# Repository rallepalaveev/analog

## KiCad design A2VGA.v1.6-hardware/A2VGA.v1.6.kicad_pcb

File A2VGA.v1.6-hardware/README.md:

A2VGA

This project is a new hardware implementation of the work done by Mark Aikens and David Kuder of the VGA analog card for Apple2.

The card is based on RPI Pico, 74LVC245 chips and a PLD. It is all through-hole. An improvement is that an ATF22V10 is used, which has sufficient I/O lines to allow that all necessaty bits of the address bus (A0-A10) are decoded for correct switching off of the ExtROM, in case the RPI firmware is using this memory. Additionally, the nLRESET signal can be fed to pin 30 of the Pico via a jumper, in case it is needed by future firmwares.

This v1.6 has IRQ capability and supports the A2USB firmware written by ThorstenB - https://github.com/ThorstenBr/A2USB 

Acknowledgements

This is a fork of David Kuder V2RetroComputing and ∀2 Retro Computing project with a new board design intended to fully support his software. The original design was posted by Mark Aikens Apple II VGA.

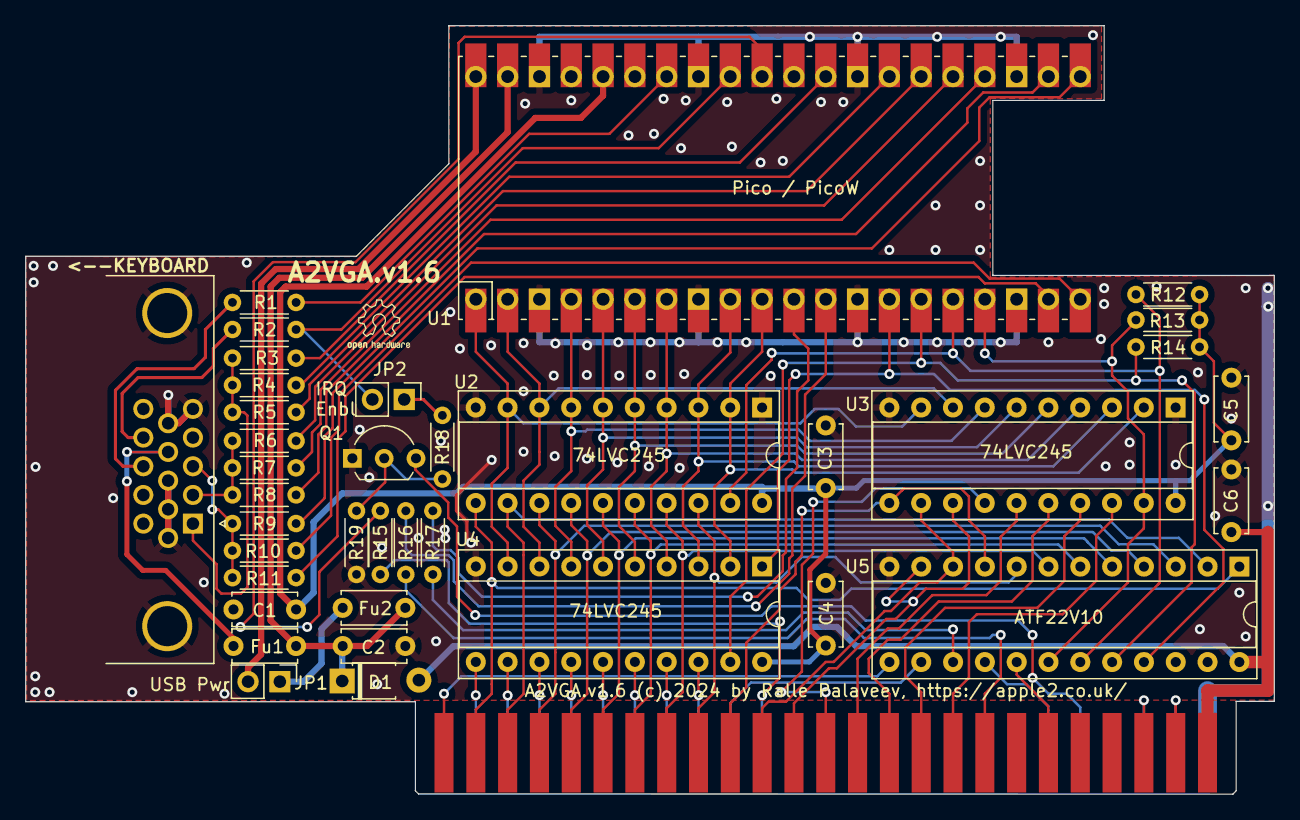
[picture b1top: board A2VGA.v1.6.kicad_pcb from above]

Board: 2 copper layers, 99.7 x 61.4 mm, 37 parts (0 on the bottom side), 49 nets.

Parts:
C1, C2, C3, C4, C5, C6: 100n; C_Disc_D5.0mm_W2.5mm_P5.00mm
CON2: DB15_Female_HighDensity_MountingHoles; DSUB-15-HD_Female_Horizontal_P2.29x1.98mm_EdgePinOffset3.03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
D1: D_T-1_P5.08mm_Horizontal
Fu1, Fu2: 500mA; C_Disc_D5.0mm_W2.5mm_P5.00mm
JP1, JP2: PinHeader_1x02_P2.54mm_Vertical
Q1: 2N7000; TO-92L_Inline_Wide
R1, R2: 47; R_Axial_DIN0204_L3.6mm_D1.6mm_P5.08mm_Horizontal
R3, R6, R9: 510; R_Axial_DIN0204_L3.6mm_D1.6mm_P5.08mm_Horizontal
R4, R7, R10, R15, R16, R17, R18: 1k; R_Axial_DIN0204_L3.6mm_D1.6mm_P5.08mm_Horizontal
R5, R8, R11: 2k; R_Axial_DIN0204_L3.6mm_D1.6mm_P5.08mm_Horizontal
R12, R13, R14, R19: 10k; R_Axial_DIN0204_L3.6mm_D1.6mm_P5.08mm_Horizontal
U1: Pico / PicoW; RPi_PicoW_SMD_TH
U2, U3, U4: 74LVC245; DIP-20_W7.62mm_Socket
U5: ATF22V10; DIP-24_W7.62mm_Socket

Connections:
3.3V: C1.1, C3.1, C4.1, C5.1, R12.2, R13.2, R14.2, U1.36 (3V3), U2.20, U3.20, U4.20
5V: C6.2, D1.2, U5.24
A0: U2.11, U5.1
A1: U2.12, U5.2
A2: U2.13, U5.3
A3: U2.14, U5.4
A4: U2.15, U5.5
A5: U2.16, U5.6
A6: U2.17, U5.7
A7: U2.18, U5.8
A8: U3.11, U5.9
A9: U3.12, U5.10
A10: U3.13, U5.11
B0: R9.2, U1.21 (GPIO16)
B1: R10.2, U1.20 (GPIO15)
B2: R11.2, U1.19 (GPIO14)
B_out: CON2.3, R9.1, R10.1, R11.1
DATADIR: U1.14 (GPIO10), U4.1, U5.21
DATAOE: R14.1, U1.15 (GPIO11), U4.19, U5.20
Enable: R17.1, U5.15
G0: R6.2, U1.25 (GPIO19)
G1: R7.2, U1.24 (GPIO18)
G2: R8.2, U1.22 (GPIO17)
GND: C1.2, C2.1, C3.2, C4.2, C5.2, C6.1, CON2.0, CON2.5, CON2.6, CON2.7, CON2.8, CON2.10, Q1.1, R19.1, U1.3 (GND), U1.8 (GND), U1.13 (GND), U1.18 (GND), U1.23 (GND), U1.28 (GND), U1.33 (AGND), U1.38 (GND), U2.1, U2.10, U3.1, U3.10, U4.10, U5.12
G_out: CON2.2, R6.1, R7.1, R8.1
HSYNC: R1.2, U1.34 (GPIO28_ADC2)
HS_out: CON2.13, R1.1
L-ENBL: R17.2, U1.11 (GPIO8)
L-PHI0: R15.2, U1.31 (GPIO26_ADC0)
L-RW: R16.2, U1.12 (GPIO9)
LD0: U1.1 (GPIO0), U2.9, U3.9, U4.9
LD1: U1.2 (GPIO1), U2.8, U3.8, U4.8
LD2: U1.4 (GPIO2), U2.7, U3.7, U4.7
LD3: U1.5 (GPIO3), U2.6, U3.6, U4.6
LD4: U1.6 (GPIO4), U2.5, U3.5, U4.5
LD5: U1.7 (GPIO5), U2.4, U3.4, U4.4
LD6: U1.9 (GPIO6), U2.3, U3.3, U4.3
LD7: U1.10 (GPIO7), U2.2, U3.2, U4.2
LSBOE: R12.1, U1.16 (GPIO12), U2.19, U5.19
MSBOE: R13.1, U1.17 (GPIO13), U3.19, U5.18
R0: R3.2, U1.29 (GPIO22)
R1: R4.2, U1.27 (GPIO21)
R2: R5.2, U1.26 (GPIO20)
RGB-PWR: CON2.9, Fu1.1
R_out: CON2.1, R3.1, R4.1, R5.1
VBUS: JP1.2, U1.40 (VBUS)
VSYNC: JP2.2, R2.2, U1.32 (GPIO27_ADC1)
VSYS: C2.2, D1.1, Fu1.2, Fu2.2, U1.39 (VSYS)
VS_out: CON2.14, R2.1

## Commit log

2024-07-07 Rename A2VGA.v1.6-hardware/v2-analog-preloader.uf2 to A2VGA.v1.6-hardware/firmwares/v2-analog-preloader.uf2
2024-07-07 Rename A2VGA.v1.6-hardware/A2USB-MOUSE-PAL-A2VGA-4ns-v1.3.uf2 to A2VGA.v1.6-hardware/firmwares/A2USB-MOUSE-PAL-A2VGA-4ns-v1.3.uf2
2024-07-07 Rename A2VGA.v1.6-hardware/v2-analog-lc-4ns-vga.uf2 to A2VGA.v1.6-hardware/firmwares/v2-analog-lc-4ns-vga.uf2
2024-07-07 Rename A2VGA.v1.6-hardware/v2-analog-lc-4ns-z80.uf2 to A2VGA.v1.6-hardware/firmwares/v2-analog-lc-4ns-z80.uf2

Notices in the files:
A2VGA.v1.6-hardware/A2VGA.v1.6.kicad_pcb:
A2VGA.v1.6, board design by R.Palaveev (c) 2024
Apple II VGA by Mark Aikens, (c) 2021-2022 &
V2 Analog by David Kuder, (c) 2022-2023
A2VGA.v1.6 (c) 2024 by Ralle Palaveev, https://apple2.co.uk
